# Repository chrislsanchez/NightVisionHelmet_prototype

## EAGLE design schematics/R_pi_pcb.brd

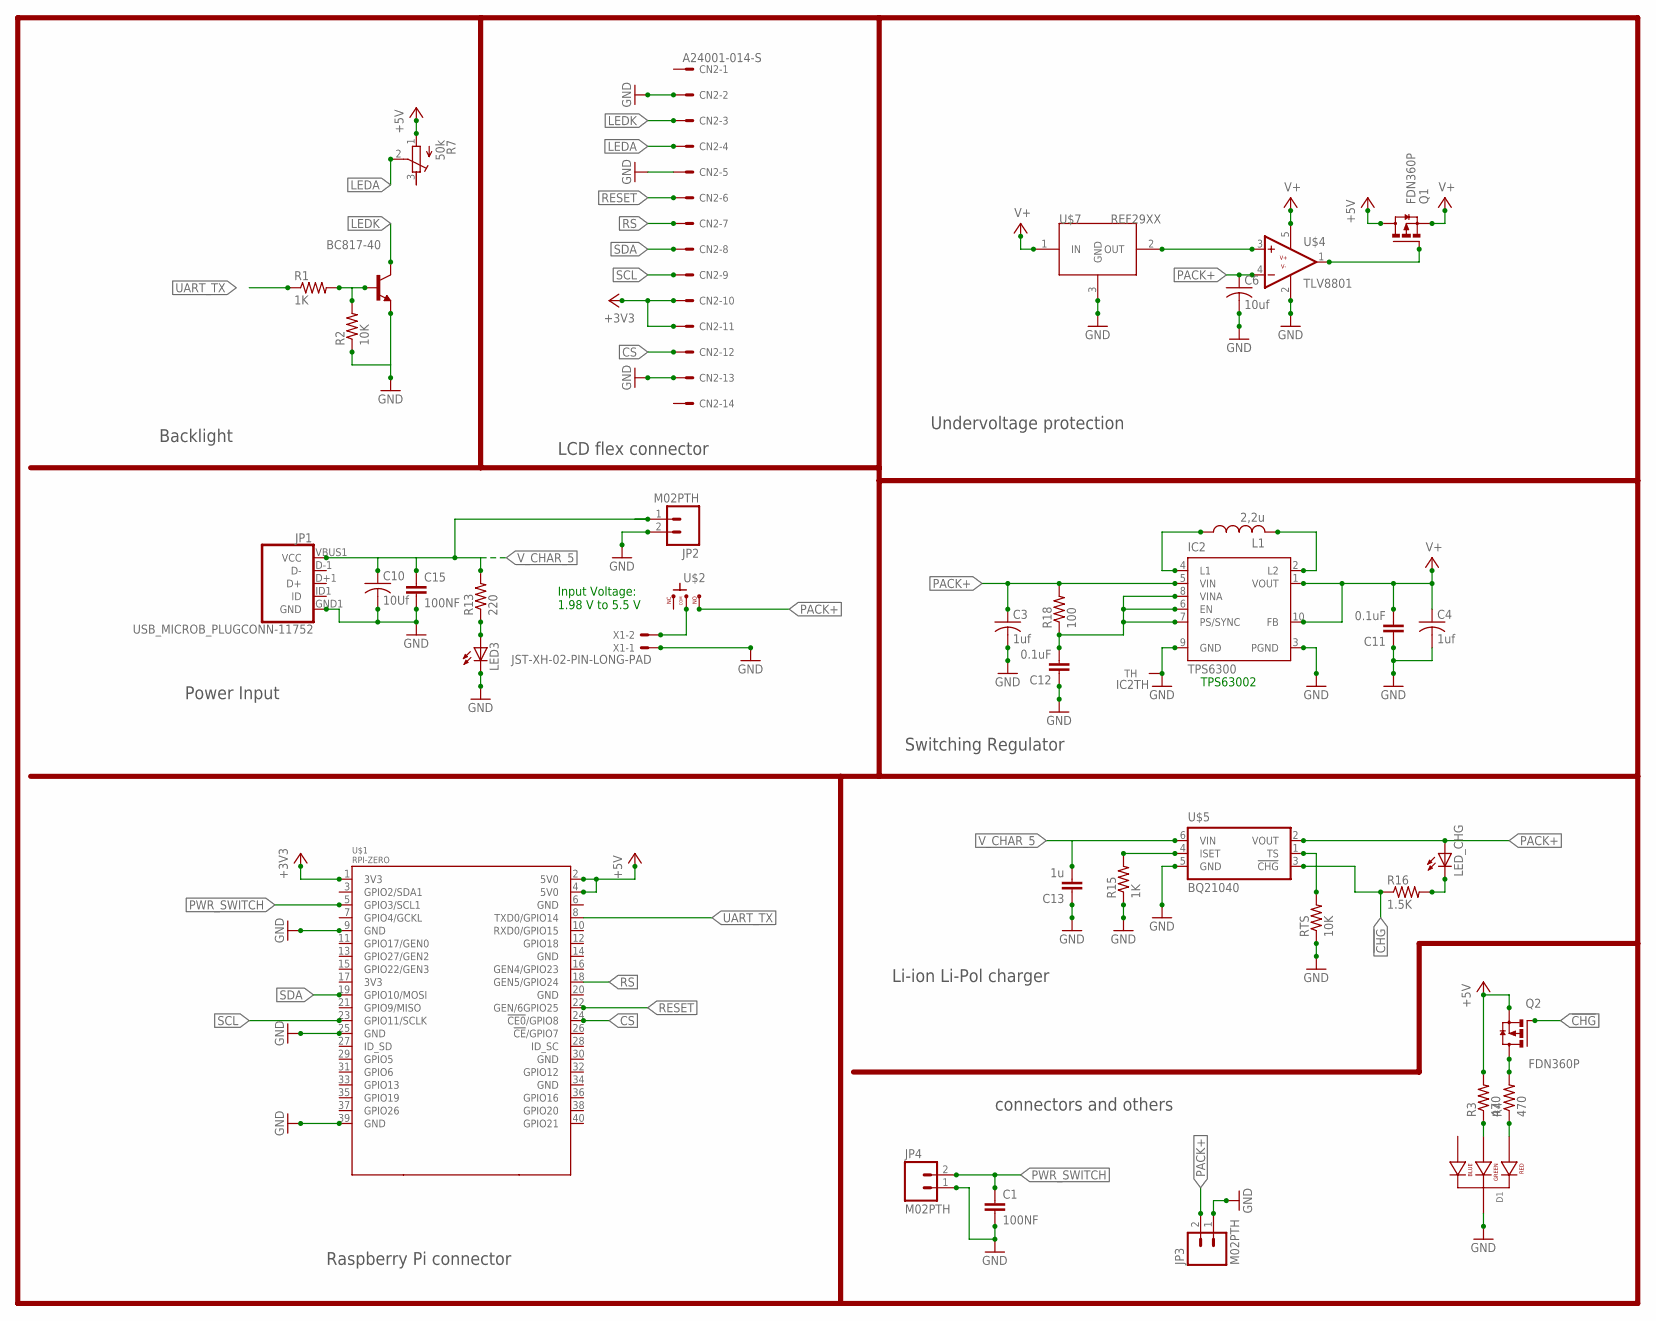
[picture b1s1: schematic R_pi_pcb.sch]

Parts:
BC817-40: BC817-40-NPN-SOT23-BEC; SOT23-BEC
C1, C15: 100NF; C0805
C3, C4: 1uf; C1206K
C6: 10uf; C1206K
C10: 10Uf; C1206
C11, C12: 0.1uF; C0805
C13: 1u; C1206K
CN2: A24001-014-S; A24001-014
D1: LED-RGB-CC-THRUDIFFUSE; LED-RGB-THRU
IC2: TPS6300; DRC-S-PVSON-N10
JP1: USB_MICROB_PLUGCONN-11752; USB-B-MICRO-SMD_V03
JP2, JP3, JP4: M02PTH; 1X02
L1: 2,2u; L1812
LED3: LEDCHIP-LED0805; CHIP-LED0805
LED_CHG: LEDCHIP-LED0805; CHIP-LED0805
Q1, Q2: FDN360P; SUPER-SOT3
R1, R15: 1K; R0805
R2: 10K; R0805
R3, R4: 470; R0805
R7: 50k; RTRIM64P
R13: 220; R0805
R16: 1.5K; R0805
R18: 100; R0805
RTS: 10K; R0805
U$1: RPI-ZERO; RASPBERRYPI_BASTELSTUBE_V13_RASPI_BOARD_B+_FULL
U$2: -SWITCH; CON3
U$4: TLV8801; SOT23-5
U$5: BQ21040; SOT23-6
U$7: REF29XX; SOT23
X1: JST-XH-02-PIN-LONG-PAD; JST-XH-02-PACKAGE-LONG-PAD

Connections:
!CHG: Q2.1 (G), R16.1, U$5.3 (!CHG)
+3V3: CN2.10, CN2.11, U$1.1 (3V3)
+5V: Q1.3 (D), Q2.2 (S), R3.2, R7.1 (A), U$1.2 (5V0), U$1.4 (5V0)
CS: CN2.12, U$1.24 (!CE0!/GPIO8)
GND: BC817-40.E, C1.2, C3.2, C4.2, C6.2, C10.2, C11.1, C12.1, C13.1, C15.2, CN2.2, CN2.5, CN2.13, D1.2 (CATHODE), IC2.3 (PGND), IC2.9 (GND), IC2.TH, JP1.GND1 (GND), JP2.2, JP3.1, JP4.1, LED3.C, R2.1, R15.1, RTS.1, U$1.9 (GND), U$1.25 (GND), U$1.39 (GND), U$4.2 (V-), U$5.5 (GND), U$7.3 (GND), X1.1
LEDA: CN2.4, R7.2 (S)
LEDK: BC817-40.C, CN2.3
unnamed: U$2.P$2 (2), X1.2
unnamed: U$4.3 (+IN), U$7.2 (OUT)
unnamed: C12.2, IC2.6 (EN), IC2.7 (PS/SYNC), IC2.8 (VINA), R18.1
unnamed: Q1.1 (G), U$4.1 (OUT)
unnamed: D1.3 (GREEN_CATHODE), R3.1
unnamed: BC817-40.B, R1.2, R2.2
unnamed: D1.1 (RED_CATHODE), R4.1
unnamed: Q2.3 (D), R4.2
unnamed: IC2.4 (L1), L1.1
unnamed: LED3.A, R13.1
unnamed: IC2.2 (L2), L1.2
unnamed: R15.2, U$5.4 (ISET)
unnamed: RTS.2, U$5.1 (TS)
unnamed: LED_CHG.C, R16.2
PACK+: C3.1, C6.1, IC2.5 (VIN), JP3.2, LED_CHG.A, R18.2, U$2.P$3 (3), U$4.4 (-IN), U$5.2 (VOUT)
PWR_SWITCH: C1.1, JP4.2, U$1.5 (GPIO3/SCL1)
RESET: CN2.6, U$1.22 (GEN/6GPIO25)
RS: CN2.7, U$1.18 (GEN5/GPIO24)
SCL: CN2.9, U$1.23 (GPIO11/SCLK)
SDA: CN2.8, U$1.19 (GPIO10/MOSI)
UART_TX: R1.1, U$1.8 (TXD0/GPIO14)
V+: C4.1, C11.2, IC2.1 (VOUT), IC2.10 (FB), Q1.2 (S), U$4.5 (V+), U$7.1 (IN)
V_CHAR_5: C10.1, C13.2, C15.1, JP1.VBUS1 (VCC), JP2.1, R13.2, U$5.6 (VIN)

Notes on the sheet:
Input Voltage: 1.98 V to 5.5 V
Power Input
Switching Regulator
Li-ion Li-Pol charger
TPS63002
Undervoltage protection
LCD flex connector
Backlight
connectors and others
Raspberry Pi connector

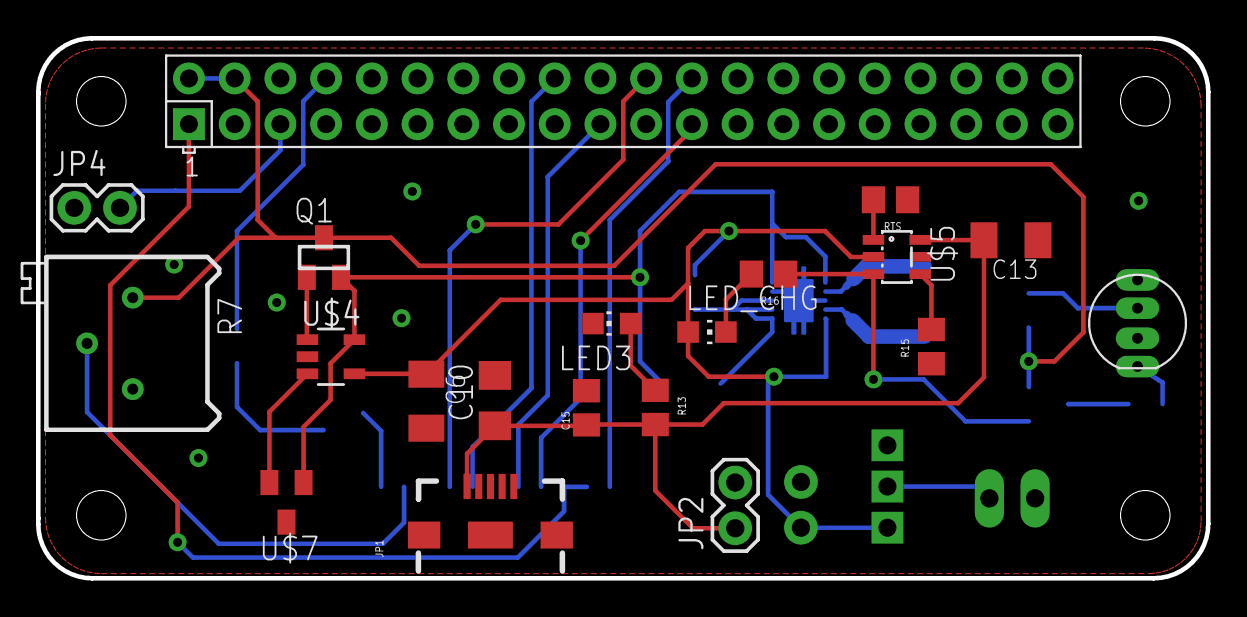
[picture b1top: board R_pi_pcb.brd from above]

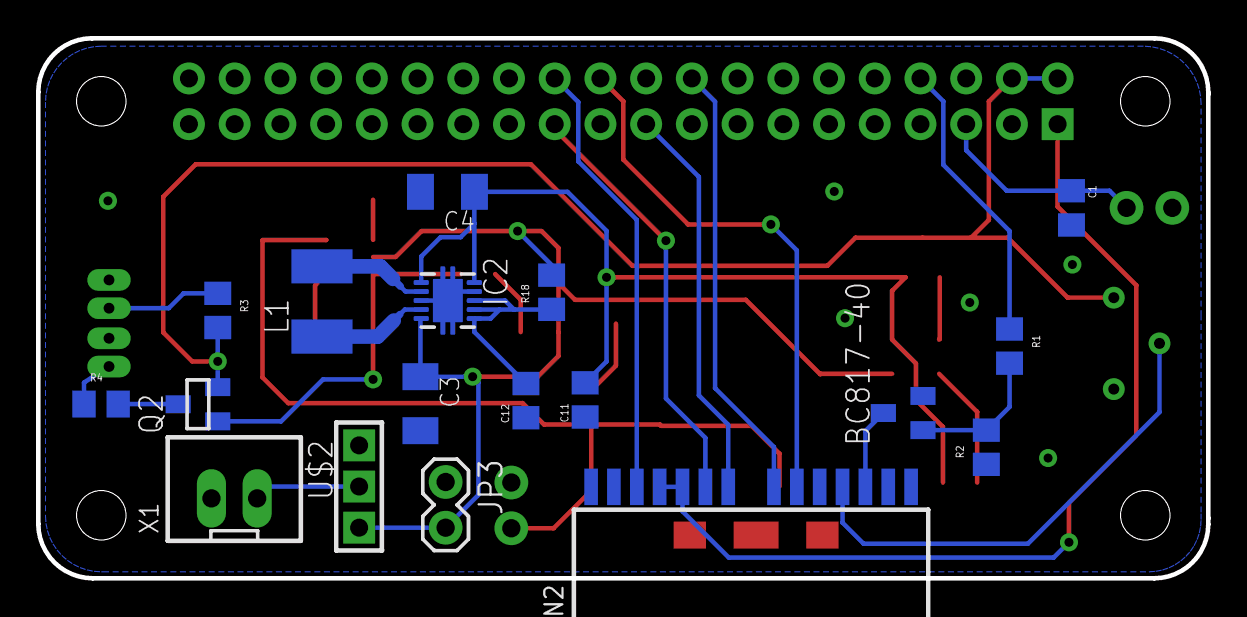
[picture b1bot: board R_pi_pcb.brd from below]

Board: 2 copper layers, 65.0 x 30.0 mm, 38 parts (18 on the bottom side), 30 nets.

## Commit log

2022-03-05 Update: - Created python and shell scripts - Added images for documentation - Appended eagle circuit schematics
    TODO: write how to use in README

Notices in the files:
parts and their libraries:
SparkFun-Connectors: Licensing: CC v3.0 Share-Alike You are welcome to use this library for commercial purposes.
